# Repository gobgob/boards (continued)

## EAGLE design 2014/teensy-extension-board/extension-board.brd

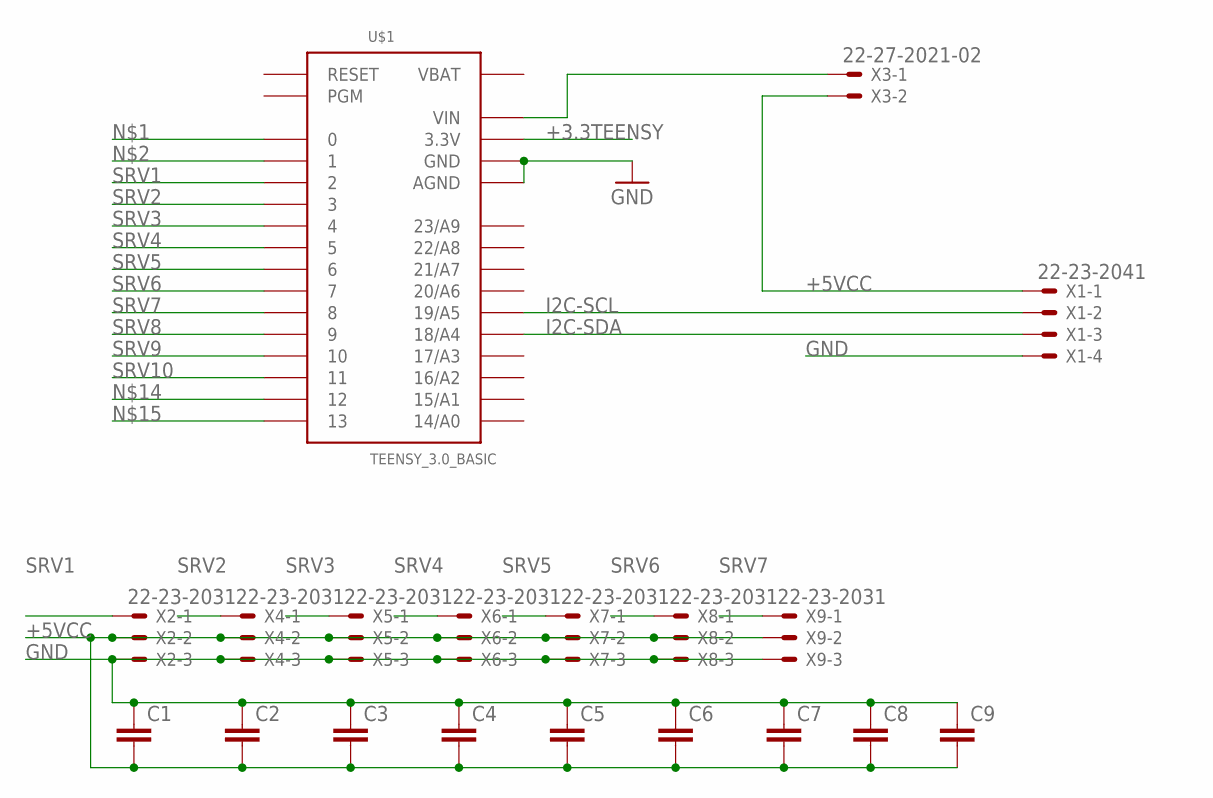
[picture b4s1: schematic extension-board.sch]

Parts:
C1, C2, C3, C4, C5, C6, C7, C8, C9: C-EUC0805K; C0805K
U$1: TEENSY_3.0_BASIC
X1: 22-23-2041
X2, X4, X5, X6, X7, X8, X9: 22-23-2031
X3: 22-27-2021-02; 6410-02

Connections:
+3.3TEENSY: U$1.3.3V, U$1.3.3V1 (3.3V)
+5VCC: C1.2, C2.2, C3.2, C4.2, C5.2, C6.2, C7.2, C8.2, C9.2, X1.1, X2.2, X3.2, X4.2, X5.2, X6.2, X7.2, X8.2, X9.2
GND: C1.1, C2.1, C3.1, C4.1, C5.1, C6.1, C7.1, C8.1, C9.1, U$1.AGND, U$1.GND, U$1.GND1 (GND), X1.4, X2.3, X4.3, X5.3, X6.3, X7.3, X8.3, X9.3
I2C-SCL: U$1.19/A5, X1.2
I2C-SDA: U$1.18/A4, X1.3
unnamed: U$1.VIN, X3.1
SRV1: U$1.2, X2.1
SRV2: U$1.3, X4.1
SRV3: U$1.4, X5.1
SRV4: U$1.5, X6.1
SRV5: U$1.6, X7.1
SRV6: U$1.7, X8.1
SRV7: U$1.8, X9.1
SRV8: U$1.9
SRV9: U$1.10
SRV10: U$1.11
VBAT: U$1.VBAT

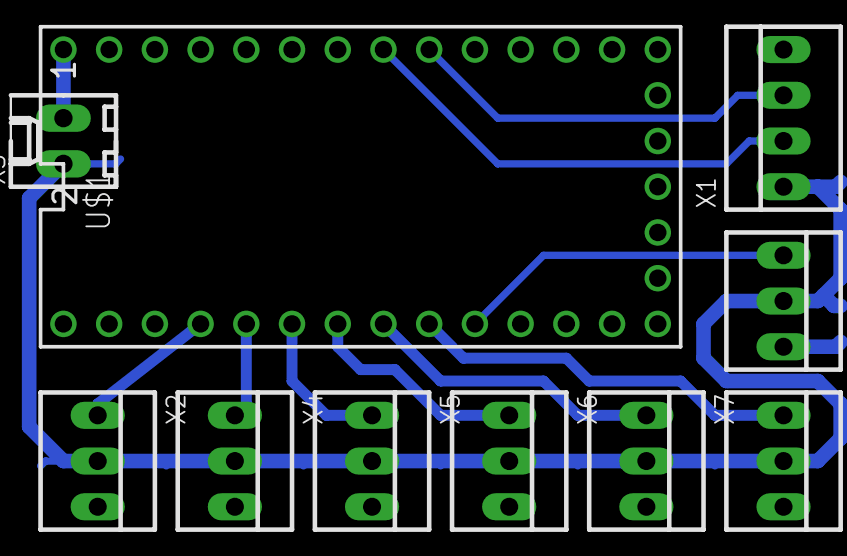
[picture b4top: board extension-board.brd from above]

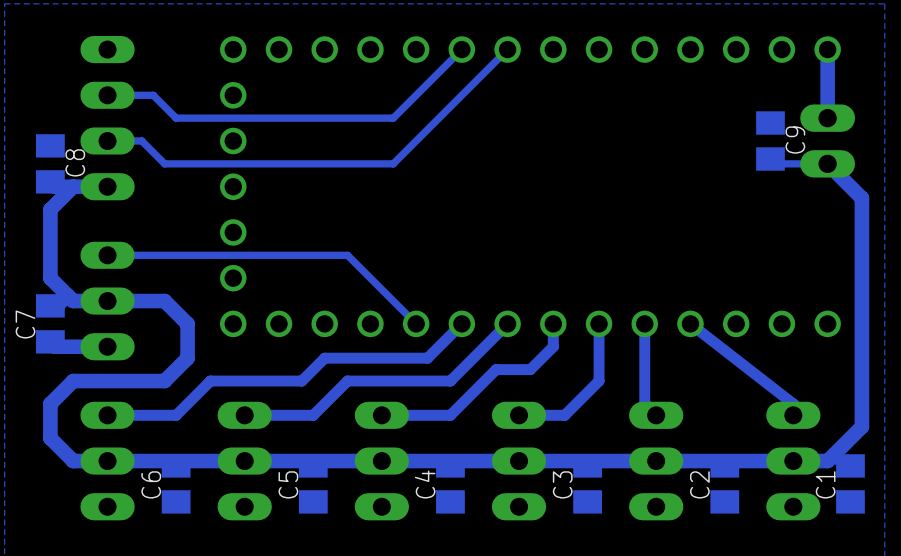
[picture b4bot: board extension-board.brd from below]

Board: 2 copper layers, 19 parts (9 on the bottom side), 13 nets.

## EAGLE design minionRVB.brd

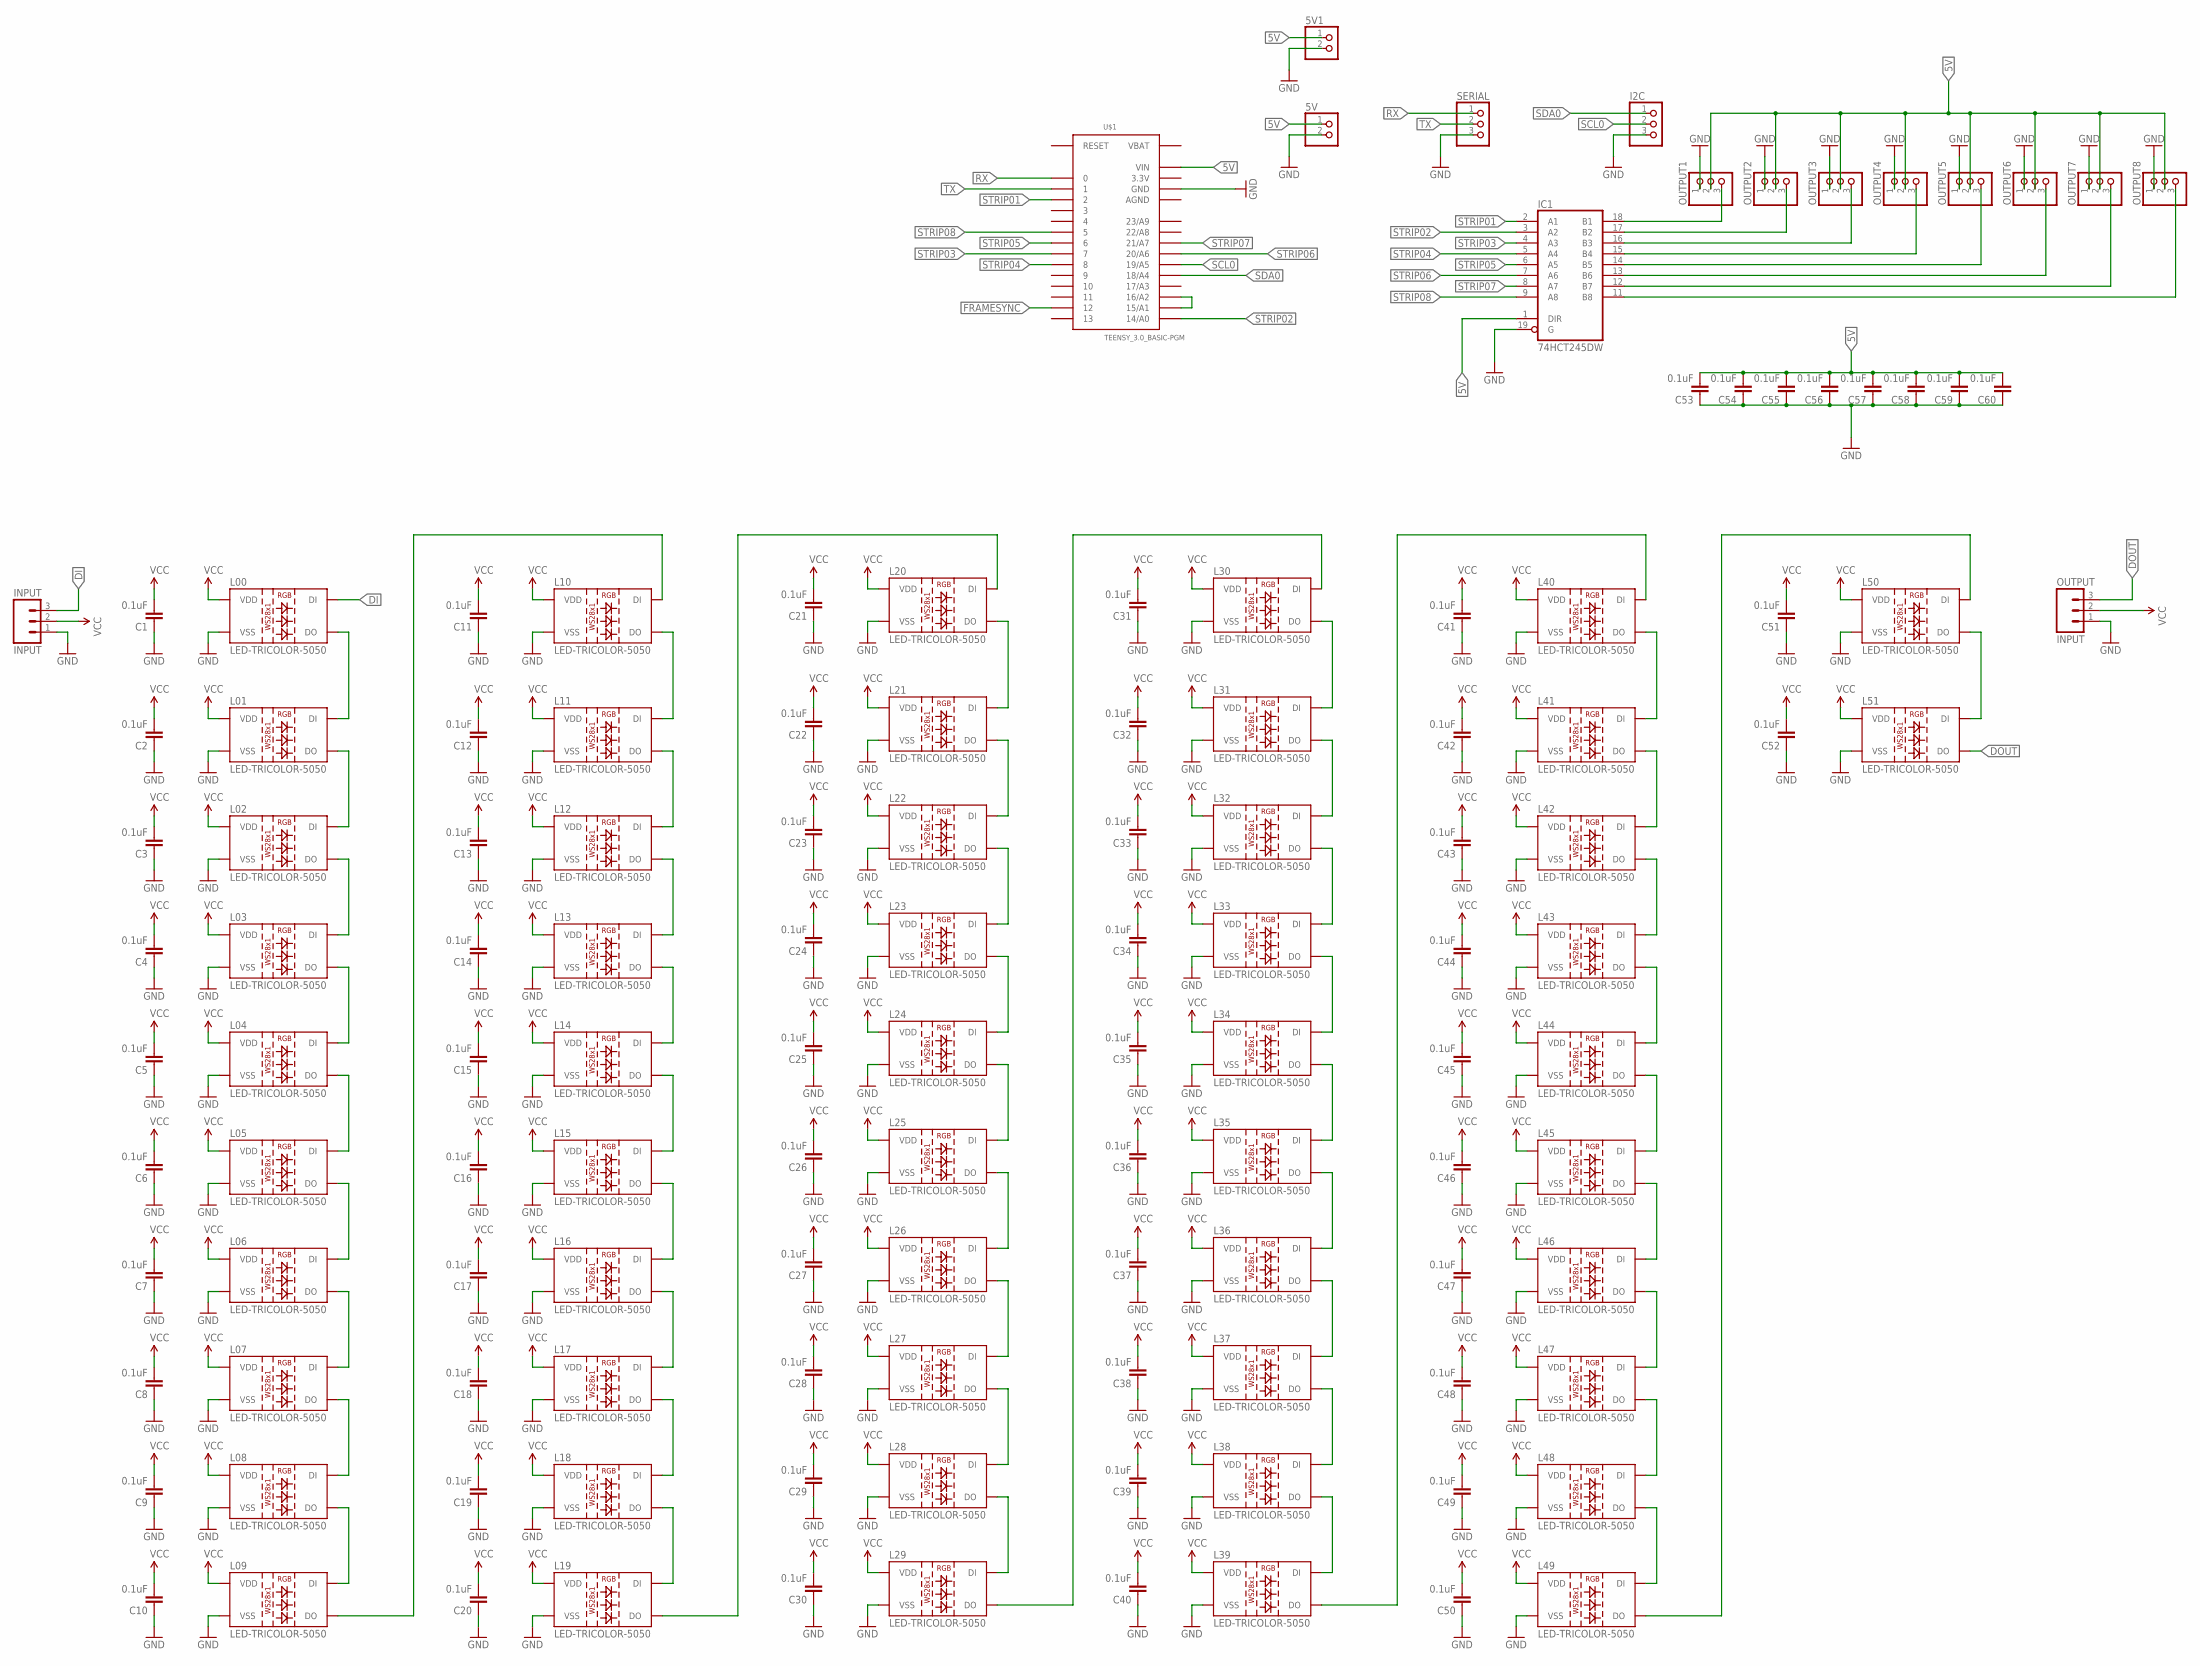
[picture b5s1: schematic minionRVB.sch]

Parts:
5V, 5V1: PINHD-1X2; 1X02
C1, C2, C3, C4, C5, C6, C7, C8, C9, C10, C11, C12, C13, C14, C15, C16, C17, C18, C19, C20, C21, C22, C23, C24, C25, C26, C27, C28, C29, C30, C31, C32, C33, C34, C35, C36, C37, C38, C39, C40, C41, C42, C43, C44, C45, C46, C47, C48, C49, C50, C51, C52, C53, C54, C55, C56, C57, C58, C59, C60: 0.1uF; 0603-CAP
I2C: PINHD-1X3; 1X03
IC1: 74HCT245DW; SO20W
INPUT: INPUT; 1X03
L00, L01, L02, L03, L04, L05, L06, L07, L08, L09, L10, L11, L12, L13, L14, L15, L16, L17, L18, L19, L20, L21, L22, L23, L24, L25, L26, L27, L28, L29, L30, L31, L32, L33, L34, L35, L36, L37, L38, L39, L40, L41, L42, L43, L44, L45, L46, L47, L48, L49, L50, L51: LED-TRICOLOR-5050; LED-TRICOLOR-5050-IC
OUTPUT: INPUT; 1X03
OUTPUT1, OUTPUT2, OUTPUT3, OUTPUT4, OUTPUT5, OUTPUT6, OUTPUT7, OUTPUT8: PINHD-1X3; 1X03
SERIAL: PINHD-1X3; 1X03
U$1: TEENSY_3.0_BASIC-PGM

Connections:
3.3V: U$1.3.3V, U$1.3.3V1 (3.3V)
5V: 5V.1, 5V1.1, C53.2, C54.2, C55.2, C56.2, C57.2, C58.2, C59.2, C60.2, IC1.1 (DIR), OUTPUT1.2, OUTPUT2.2, OUTPUT3.2, OUTPUT4.2, OUTPUT5.2, OUTPUT6.2, OUTPUT7.2, OUTPUT8.2, U$1.VIN
AGND: U$1.AGND
DI: INPUT.3, L00.2 (DI)
DOUT: L51.1 (DO), OUTPUT.3
FRAMESYNC: U$1.12
GND: 5V.2, 5V1.2, C1.1, C2.1, C3.1, C4.1, C5.1, C6.1, C7.1, C8.1, C9.1, C10.1, C11.1, C12.1, C13.1, C14.1, C15.1, C16.1, C17.1, C18.1, C19.1, C20.1, C21.1, C22.1, C23.1, C24.1, C25.1, C26.1, C27.1, C28.1, C29.1, C30.1, C31.1, C32.1, C33.1, C34.1, C35.1, C36.1, C37.1, C38.1, C39.1, C40.1, C41.1, C42.1, C43.1, C44.1, C45.1, C46.1, C47.1, C48.1, C49.1, C50.1, C51.1, C52.1, C53.1, C54.1, C55.1, C56.1, C57.1, C58.1, C59.1, C60.1, I2C.3, IC1.10 (GND), IC1.19 (G), INPUT.1, L00.6 (VSS), L01.6 (VSS), L02.6 (VSS), L03.6 (VSS), L04.6 (VSS), L05.6 (VSS), L06.6 (VSS), L07.6 (VSS), L08.6 (VSS), L09.6 (VSS), L10.6 (VSS), L11.6 (VSS), L12.6 (VSS), L13.6 (VSS), L14.6 (VSS), L15.6 (VSS), L16.6 (VSS), L17.6 (VSS), L18.6 (VSS), L19.6 (VSS), L20.6 (VSS), L21.6 (VSS), L22.6 (VSS), L23.6 (VSS), L24.6 (VSS), L25.6 (VSS), L26.6 (VSS), L27.6 (VSS), L28.6 (VSS), L29.6 (VSS), L30.6 (VSS), L31.6 (VSS), L32.6 (VSS), L33.6 (VSS), L34.6 (VSS), L35.6 (VSS), L36.6 (VSS), L37.6 (VSS), L38.6 (VSS), L39.6 (VSS), L40.6 (VSS), L41.6 (VSS), L42.6 (VSS), L43.6 (VSS), L44.6 (VSS), L45.6 (VSS), L46.6 (VSS), L47.6 (VSS), L48.6 (VSS), L49.6 (VSS), L50.6 (VSS), L51.6 (VSS), OUTPUT.1, OUTPUT1.1, OUTPUT2.1, OUTPUT3.1, OUTPUT4.1, OUTPUT5.1, OUTPUT6.1, OUTPUT7.1, OUTPUT8.1, SERIAL.3, U$1.GND, U$1.GND1 (GND)
unnamed: U$1.15/A1, U$1.16/A2
unnamed: L31.1 (DO), L32.2 (DI)
unnamed: L33.1 (DO), L34.2 (DI)
unnamed: L35.1 (DO), L36.2 (DI)
unnamed: L01.1 (DO), L02.2 (DI)
unnamed: L03.1 (DO), L04.2 (DI)
unnamed: L05.1 (DO), L06.2 (DI)
unnamed: L07.1 (DO), L08.2 (DI)
unnamed: L08.1 (DO), L09.2 (DI)
unnamed: L00.1 (DO), L01.2 (DI)
unnamed: L02.1 (DO), L03.2 (DI)
unnamed: L04.1 (DO), L05.2 (DI)
unnamed: L06.1 (DO), L07.2 (DI)
unnamed: L09.1 (DO), L10.2 (DI)
unnamed: L11.1 (DO), L12.2 (DI)
unnamed: L13.1 (DO), L14.2 (DI)
unnamed: L15.1 (DO), L16.2 (DI)
unnamed: L17.1 (DO), L18.2 (DI)
unnamed: L18.1 (DO), L19.2 (DI)
unnamed: L10.1 (DO), L11.2 (DI)
unnamed: L12.1 (DO), L13.2 (DI)
unnamed: L14.1 (DO), L15.2 (DI)
unnamed: L16.1 (DO), L17.2 (DI)
unnamed: L19.1 (DO), L20.2 (DI)
unnamed: L21.1 (DO), L22.2 (DI)
unnamed: L23.1 (DO), L24.2 (DI)
unnamed: L25.1 (DO), L26.2 (DI)
unnamed: L27.1 (DO), L28.2 (DI)
unnamed: L28.1 (DO), L29.2 (DI)
unnamed: L20.1 (DO), L21.2 (DI)
unnamed: L22.1 (DO), L23.2 (DI)
unnamed: L24.1 (DO), L25.2 (DI)
unnamed: L26.1 (DO), L27.2 (DI)
unnamed: L29.1 (DO), L30.2 (DI)
unnamed: L37.1 (DO), L38.2 (DI)
unnamed: L38.1 (DO), L39.2 (DI)
unnamed: L30.1 (DO), L31.2 (DI)
unnamed: L32.1 (DO), L33.2 (DI)
unnamed: L34.1 (DO), L35.2 (DI)
unnamed: L36.1 (DO), L37.2 (DI)
unnamed: L39.1 (DO), L40.2 (DI)
unnamed: IC1.18 (B1), OUTPUT1.3
unnamed: L41.1 (DO), L42.2 (DI)
unnamed: L43.1 (DO), L44.2 (DI)
unnamed: L45.1 (DO), L46.2 (DI)
unnamed: L47.1 (DO), L48.2 (DI)
unnamed: L48.1 (DO), L49.2 (DI)
unnamed: L40.1 (DO), L41.2 (DI)
unnamed: L42.1 (DO), L43.2 (DI)
unnamed: L44.1 (DO), L45.2 (DI)
unnamed: L46.1 (DO), L47.2 (DI)
unnamed: L49.1 (DO), L50.2 (DI)
unnamed: L50.1 (DO), L51.2 (DI)
unnamed: IC1.17 (B2), OUTPUT2.3
unnamed: IC1.16 (B3), OUTPUT3.3
unnamed: IC1.15 (B4), OUTPUT4.3
unnamed: IC1.14 (B5), OUTPUT5.3
unnamed: IC1.13 (B6), OUTPUT6.3
unnamed: IC1.12 (B7), OUTPUT7.3
unnamed: IC1.11 (B8), OUTPUT8.3
RX: SERIAL.1, U$1.0
SCL0: I2C.2, U$1.19/A5
SDA0: I2C.1, U$1.18/A4
STRIP01: IC1.2 (A1), U$1.2
STRIP02: IC1.3 (A2), U$1.14/A0
STRIP03: IC1.4 (A3), U$1.7
STRIP04: IC1.5 (A4), U$1.8
STRIP05: IC1.6 (A5), U$1.6
STRIP06: IC1.7 (A6), U$1.20/A6
STRIP07: IC1.8 (A7), U$1.21/A7
STRIP08: IC1.9 (A8), U$1.5
TX: SERIAL.2, U$1.1
VBAT: U$1.VBAT
VCC: C1.2, C2.2, C3.2, C4.2, C5.2, C6.2, C7.2, C8.2, C9.2, C10.2, C11.2, C12.2, C13.2, C14.2, C15.2, C16.2, C17.2, C18.2, C19.2, C20.2, C21.2, C22.2, C23.2, C24.2, C25.2, C26.2, C27.2, C28.2, C29.2, C30.2, C31.2, C32.2, C33.2, C34.2, C35.2, C36.2, C37.2, C38.2, C39.2, C40.2, C41.2, C42.2, C43.2, C44.2, C45.2, C46.2, C47.2, C48.2, C49.2, C50.2, C51.2, C52.2, IC1.20 (VCC), INPUT.2, L00.3 (VDD), L00.5 (VDD), L01.3 (VDD), L01.5 (VDD), L02.3 (VDD), L02.5 (VDD), L03.3 (VDD), L03.5 (VDD), L04.3 (VDD), L04.5 (VDD), L05.3 (VDD), L05.5 (VDD), L06.3 (VDD), L06.5 (VDD), L07.3 (VDD), L07.5 (VDD), L08.3 (VDD), L08.5 (VDD), L09.3 (VDD), L09.5 (VDD), L10.3 (VDD), L10.5 (VDD), L11.3 (VDD), L11.5 (VDD), L12.3 (VDD), L12.5 (VDD), L13.3 (VDD), L13.5 (VDD), L14.3 (VDD), L14.5 (VDD), L15.3 (VDD), L15.5 (VDD), L16.3 (VDD), L16.5 (VDD), L17.3 (VDD), L17.5 (VDD), L18.3 (VDD), L18.5 (VDD), L19.3 (VDD), L19.5 (VDD), L20.3 (VDD), L20.5 (VDD), L21.3 (VDD), L21.5 (VDD), L22.3 (VDD), L22.5 (VDD), L23.3 (VDD), L23.5 (VDD), L24.3 (VDD), L24.5 (VDD), L25.3 (VDD), L25.5 (VDD), L26.3 (VDD), L26.5 (VDD), L27.3 (VDD), L27.5 (VDD), L28.3 (VDD), L28.5 (VDD), L29.3 (VDD), L29.5 (VDD), L30.3 (VDD), L30.5 (VDD), L31.3 (VDD), L31.5 (VDD), L32.3 (VDD), L32.5 (VDD), L33.3 (VDD), L33.5 (VDD), L34.3 (VDD), L34.5 (VDD), L35.3 (VDD), L35.5 (VDD), L36.3 (VDD), L36.5 (VDD), L37.3 (VDD), L37.5 (VDD), L38.3 (VDD), L38.5 (VDD), L39.3 (VDD), L39.5 (VDD), L40.3 (VDD), L40.5 (VDD), L41.3 (VDD), L41.5 (VDD), L42.3 (VDD), L42.5 (VDD), L43.3 (VDD), L43.5 (VDD), L44.3 (VDD), L44.5 (VDD), L45.3 (VDD), L45.5 (VDD), L46.3 (VDD), L46.5 (VDD), L47.3 (VDD), L47.5 (VDD), L48.3 (VDD), L48.5 (VDD), L49.3 (VDD), L49.5 (VDD), L50.3 (VDD), L50.5 (VDD), L51.3 (VDD), L51.5 (VDD), OUTPUT.2

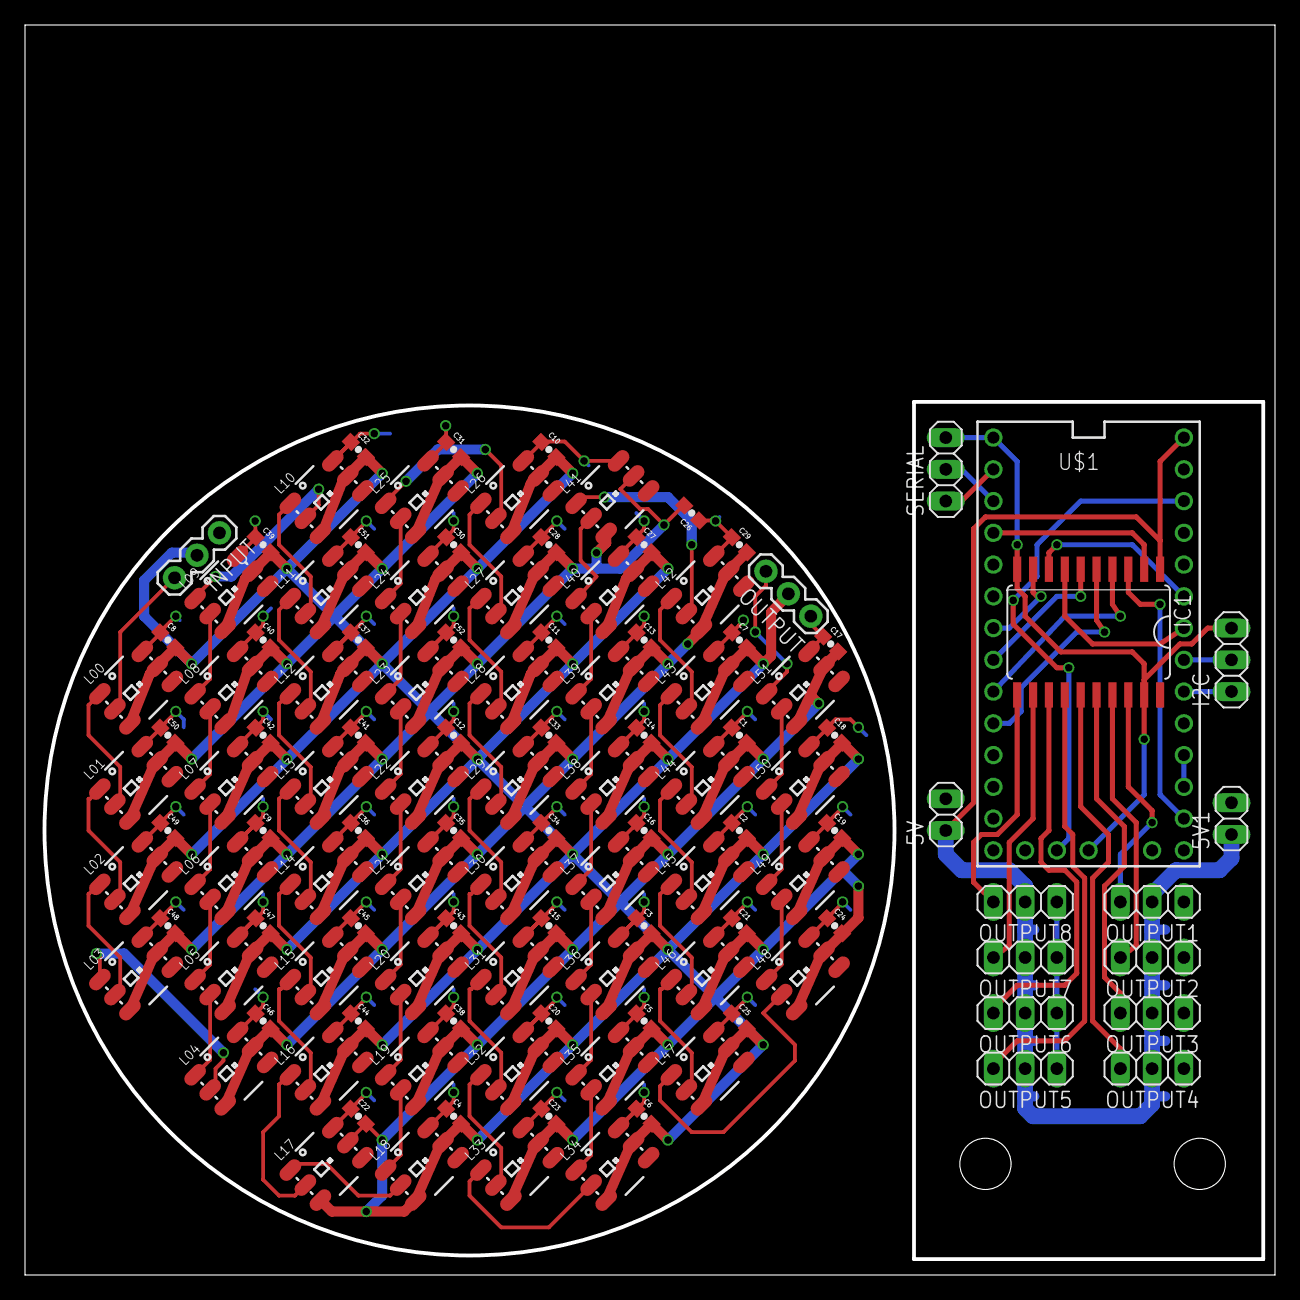
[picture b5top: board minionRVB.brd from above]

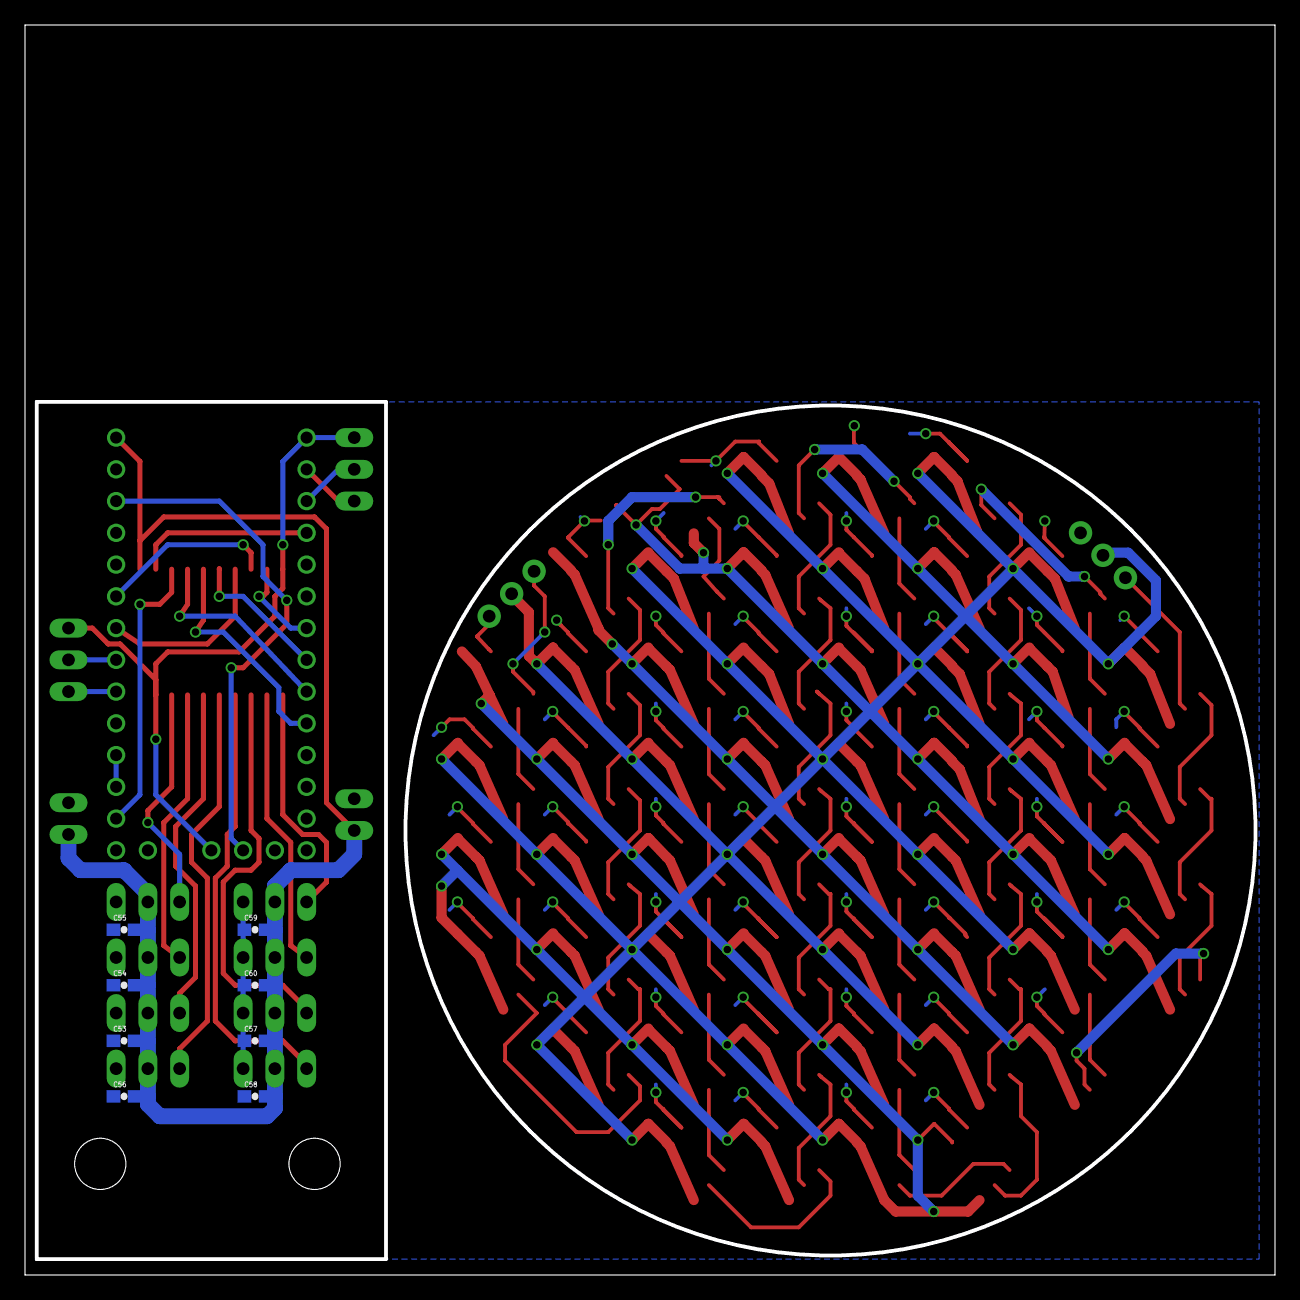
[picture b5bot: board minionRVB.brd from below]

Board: 2 copper layers, 100.0 x 100.0 mm, 128 parts (8 on the bottom side), 78 nets.
